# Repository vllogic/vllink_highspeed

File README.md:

# Vllink HighSpeed

## 简介

Vllink Highspeed是一款中低成本高性能调试器。相比Lite版，支持USB2.0高速、更好的IO时序优化、更好的CPU速度，预计JTAG/SWD接口对目标芯片SRAM速度可以达到MB/S的级别，媲美当前千元级别调试器。

## 硬件

## 功能
* JTAG/SWD接口(TDI,TMS,TCK,SRST,TDO,TRST)
* 2路独立串口(TX1,RX1,TX2,RX2)，1路共用串口(TDO,SRST)
* 4通道逻辑分析输入口(CH0,CH1,CH2,CH3)
* 具有电平转换电路，同时支持外部参考电源与内部数字可调电源1.5V至4.75V(Vdrv)
* 使用内部电源对外供电时，支持电流测量(Vdrv)
* OLED_12864(全彩LED可选)
* 远超同等价格级别硬件的Code/Data空间

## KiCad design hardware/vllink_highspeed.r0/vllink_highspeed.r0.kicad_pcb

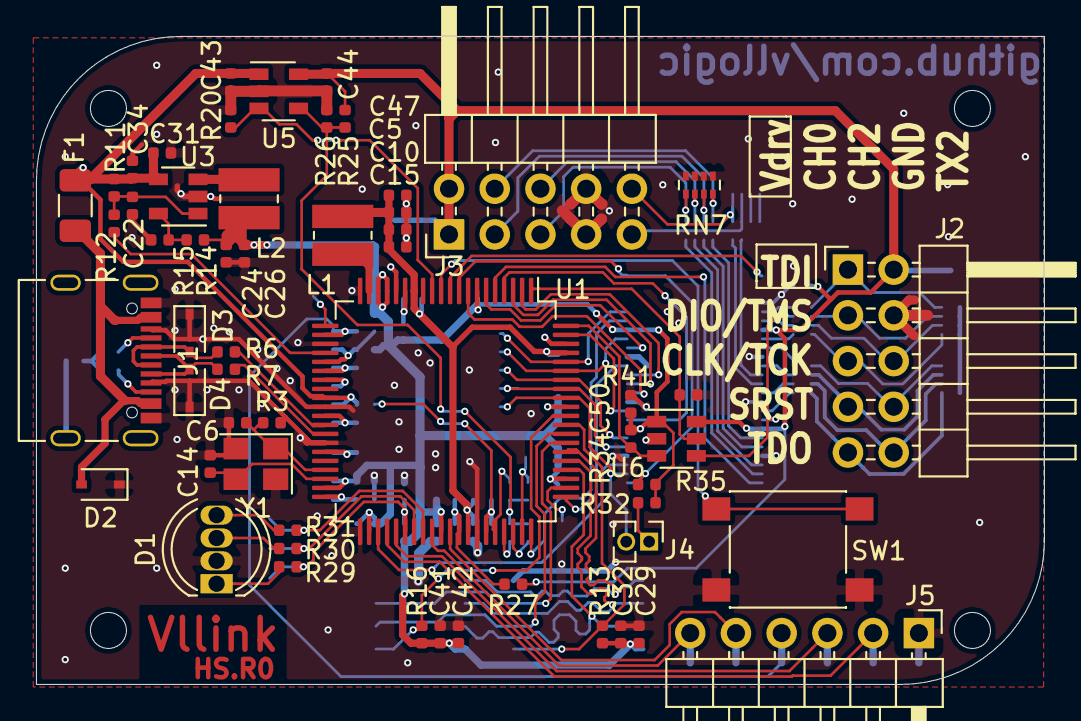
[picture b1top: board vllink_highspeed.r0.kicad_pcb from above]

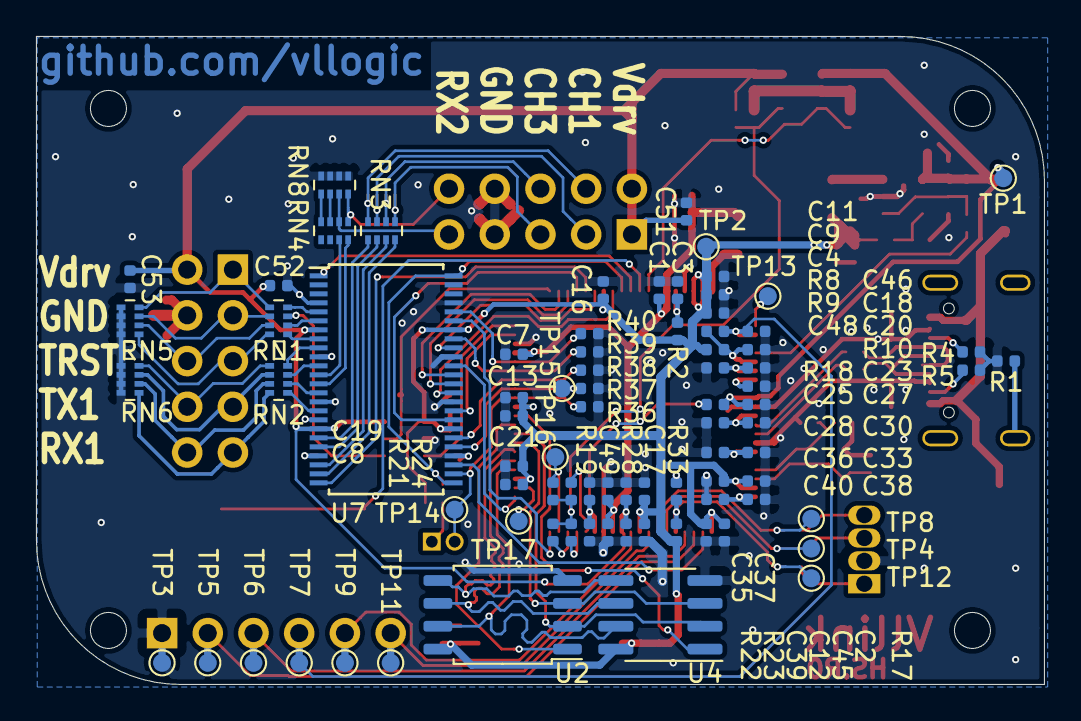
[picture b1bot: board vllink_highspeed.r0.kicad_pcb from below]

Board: 2 copper layers, 56.0 x 36.0 mm, 139 parts (82 on the bottom side), 106 nets.

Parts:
C1, C3, C4, C7, C11, C12, C15, C18, C20, C22, C26, C30, C33, C35, C38: 0.22uF; C_0402_1005Metric
C2, C8, C13, C16, C27, C29, C31, C39, C41, C45, C46, C50, C52: 0.1uF; C_0402_1005Metric
C5, C10, C24, C25, C34, C43, C44, C47, C51, C53: 10uF; C_0402_1005Metric
C6, C14: 12pF; C_0402_1005Metric
C9, C17, C19, C21, C28, C36, C40, C48, C49: 4.7uF; C_0402_1005Metric
C23, C32, C37, C42: 1uF; C_0402_1005Metric
D1: LED_RCGB; LED_D5.0mm-4_RGB
D2, D3, D4: LESD3Z5.0C; D_SOD-323
F1: Polyfuse,2A; Fuse_1206_3216Metric
J1: USB_C_Receptacle_USB2.0; USB_C_Receptacle_Palconn_UTC16-G
J2: JTAG/SWD/UART0; PinHeader_2x05_P2.54mm_Horizontal
J3: LogicIN/UART1; PinHeader_2x05_P2.54mm_Horizontal
J4: NC; PinHeader_1x02_P1.27mm_Vertical
J5: Debug; PinHeader_1x06_P2.54mm_Horizontal
L1, L2: 4.7uH; L_Wuerth_MAPI-3012
R1, R9, R10: 0; R_0402_1005Metric
R2: 30k; R_0402_1005Metric
R3: 2.2M; R_0402_1005Metric
R4, R5: 5.1k; R_0402_1005Metric
R6, R7: 22; R_0402_1005Metric
R8, R20, R33: 10k; R_0402_1005Metric
R11, R25: 100k,1%; R_0402_1005Metric
R12, R17: 10k,NC; R_0402_1005Metric
R13, R16, R35, R36, R37, R38, R39, R40, R41: 47k; R_0402_1005Metric
R14: 274k,1%; R_0402_1005Metric
R15, R18, R19, R21, R27, R28: 60.4k,1%; R_0402_1005Metric
R22: 121k,1%; R_0402_1005Metric
R23: 243k,1%; R_0402_1005Metric
R24, R26: 412k,1%; R_0402_1005Metric
R29, R30, R31, R32: 4.7k; R_0402_1005Metric
R34: 47k,NC; R_0402_1005Metric
RN1, RN2, RN3, RN4: 220; R_Array_Concave_4x0402
RN5, RN6, RN7, RN8: 220k; R_Array_Concave_4x0402
SW1: SW_Push; SW_SPST_PTS645
TP1, TP2, TP3, TP4, TP5, TP6, TP7, TP8, TP9, TP11, TP12, TP13, TP14, TP15, TP16, TP17: TestPoint; TestPoint_Pad_D1.0mm
U1: MIMXRT1011; LQFP-80_12x12mm_P0.5mm
U2: W25Q128JVS; SOIC-8_5.23x5.23mm_P1.27mm
U3: ETA3486; SOT-23-5
U4: PSRAM, NC; SOIC-8_3.9x4.9mm_P1.27mm
U5: SGM2019-ADJ; SOT-23-5
U6: 74LVC1T45GW; SOT-23-6
U7: 74ALVC164245DGG; TSSOP-48_6.1x12.5mm_P0.5mm
Y1: 24M, 12pF; Crystal_SMD_3225-4Pin_3.2x2.5mm

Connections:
/BOOT_CFG0: R38.2, U1.74, U7.30
/BOOT_CFG1: R39.2, U1.75, U7.41
/BOOT_CFG2: R40.2, U1.76, U7.44
/BOOT_MODE0: J4.2, R36.2, TP14.1, U1.72, U7.26
/BOOT_MODE1: R37.2, TP15.1, U1.73, U7.29
/DCDC_3V3: C2.1, C4.1, C8.1, C9.1, C11.1, C13.1, C16.1, C17.1, C19.1, C21.1, C24.1, C26.1, C29.1, C32.1, C33.1, C35.1, C36.1, C37.1, C41.1, C42.1, C50.2, L2.1, R2.1, R9.2, R13.1, R14.1, R16.1, R17.1, R32.2, R34.1, R35.2, TP2.1, U1.7, U1.17, U1.18, U1.39, U1.42, U1.50, U1.63, U1.71, U2.8, U4.8, U6.1, U7.31, U7.42
/DCDC_SWITCH: C3.1, R2.2, U1.15
/FIO_LOGIC3: U1.43, U7.27
/FIO_TDO|UART2_RX: U1.79, U7.33
/FIO_TMS_DIR: R41.2, U1.1, U6.5
/FIO_TMS_I: U1.4, U7.32
/FIO_TMS_O: R34.2, U1.80, U6.3
/FIO|UART1_RX: U1.3, U7.36
/FIO|UART1_TX: U1.2, U7.37
/FSPI_A_CLK: U1.65, U2.6, U4.6
/FSPI_A_D0: U1.66, U2.5, U4.5
/FSPI_A_D1: U1.68, U2.2, U4.2
/FSPI_A_D2: U1.67, U2.3, U4.3
/FSPI_A_D3: U1.64, U2.7, U4.7
/FSPI_A_DQS: TP17.1, U1.62
/FSPI_A_SS0: R13.2, U1.69, U2.1
/FSPI_A_SS1: R16.2, U1.70, U4.1
/GIO_IN_DIR: U1.5, U7.24
/GIO_OE: R35.1, U1.9, U7.25, U7.48
/GIO_OUT_DIR: U1.10, U7.1
/GIO_SRST: U1.61, U7.38
/GIO_TRST|UART2_TX: U1.60, U7.43
/IO_TMS: RN1.3, U6.4, U7.17
/I_LOGIC0: RN3.2, U7.20
/I_LOGIC1: RN3.1, U7.19
/I_LOGIC2: RN3.4, U7.23
/I_LOGIC3: RN3.3, U7.22
/I_RX1: RN2.2, U7.14
/I_RX2: RN4.4, U7.13
/I_TDO: RN2.1, U7.16
/JTAG_MOD: R17.2, R29.2, R33.2, TP12.1, U1.46
/JTAG_TCK: J5.3, TP6.1, U1.45
/JTAG_TDI: R30.2, TP4.1, U1.47
/JTAG_TDO: R31.2, TP8.1, U1.48
/JTAG_TMS: J5.2, TP5.1, U1.44
/JTAG_TRSTB: J5.6, TP11.1, U1.49
/KEY: SW1.1, U1.11
/LOGIC_IN0: J3.3, RN3.7, RN7.3
/LOGIC_IN1: J3.4, RN3.8, RN7.4
/LOGIC_IN2: J3.5, RN3.5, RN7.1
/LOGIC_IN3: J3.6, RN3.6, RN7.2
/ONOFF: TP13.1, U1.21
/OTG1_DN: R6.1, U1.32
/OTG1_DP: R7.1, U1.33
/O_SRST: RN2.3, U7.11
/O_TCK: RN1.1, U7.8
/O_TDI: RN1.4, U7.5
/O_TRST: RN1.2, U7.6
/O_TX1: RN2.4, U7.9
/O_TX2: RN4.3, U7.12
/PMIC_ON_REQ: R12.2, U1.24
/POR_B: C46.1, J5.4, R8.1, TP7.1, U1.22
/RX.1: J2.10, RN2.7, RN6.2
/RX.2: J3.10, RN4.5, RN8.4
/SRST|SWRST: J2.7, RN2.6, RN6.3
/TCK|SWCLK: J2.5, RN1.8, RN5.1
/TDI: J2.1, RN1.5, RN5.4
/TDO|SWO: J2.9, RN2.8, RN6.1
/TMS|SWDIO: J2.3, RN1.6, RN5.3
/TRACE_SWO: R21.2, TP16.1, U1.59
/TRST: J2.6, RN1.7, RN5.2
/TX.1: J2.8, RN2.5, RN6.4
/TX.2: J3.9, RN4.6, RN8.3
/UART3_RX: J5.5, TP9.1, U1.51
/UART4_RX: U1.8, U7.35
/UART4_TX: U1.6, U7.40
/USB_5V: C23.1, C31.1, C34.1, C43.1, F1.1, R11.2, R18.1, TP1.1, U1.29, U3.4, U5.1
/USB_DN: D3.2, J1.A7, J1.B7, R6.2
/USB_DP: D4.2, J1.A6, J1.B6, R7.2
/VBUS_AD: C39.1, R18.2, R19.1, U1.55
/VDD_SNVS_IN: C18.1, R8.2, R9.1, U1.25
/VDD_SOC_IN: C1.1, C5.1, C7.1, C10.1, C12.1, C15.1, C47.1, C49.1, L1.1, U1.14, U1.53, U1.77
/Vdirve_AD: C45.1, R27.2, R28.1, U1.52
/Vdrive_CTRL2: R22.2, U1.58
/Vdrive_CTRL3: R23.2, U1.57
/Vdrive_CTRL4: R24.2, U1.56
/Vdrive_EN: R20.1, U1.12, U5.3
/XTALI: C6.1, R3.1, U1.37, Y1.1
/XTALO: C14.1, U1.38, Y1.3
GND: C1.2, C2.2, C3.2, C4.2, C5.2, C6.2, C7.2, C8.2, C9.2, C10.2, C11.2, C12.2, C13.2, C14.2, C15.2, C16.2, C17.2, C18.2, C19.2, C20.2, C21.2, C22.2, C23.2, C24.2, C25.2, C26.2, C27.2, C28.2, C29.2, C30.2, C31.2, C32.2, C33.2, C34.2, C35.2, C36.2, C37.2, C38.2, C39.2, C40.2, C41.2, C42.2, C43.2, C44.2, C45.2, C46.2, C47.2, C48.2, C49.2, C50.1, C51.2, C52.1, C53.2, D1.2, D2.1, D3.1, D4.1, J1.A1, J1.A8, J1.A12, J1.B1, J1.B8, J1.B12, J2.4, J3.7, J3.8, J5.1, R1.2, R3.2, R4.1, R5.1, R10.2, R15.2, R19.2, R20.2, R26.2, R28.2, R33.1, R36.1, R37.1, R38.1, R39.1, R40.1, R41.1, RN5.5, RN5.6, RN5.7, RN5.8, RN6.5, RN6.6, RN6.7, RN6.8, RN7.5, RN7.6, RN7.7, RN7.8, RN8.5, RN8.6, RN8.7, RN8.8, SW1.2, TP3.1, U1.16, U1.20, U1.23, U1.30, U1.34, U1.41, U1.54, U1.78, U2.4, U3.2, U4.4, U5.2, U6.2, U7.4, U7.10, U7.15, U7.21, U7.28, U7.34, U7.39, U7.45, Y1.2, Y1.4
unnamed: C20.1, C48.1, U1.26
unnamed: C22.1, R11.1, R12.1, U3.1
unnamed: C25.1, C27.1, U1.31
unnamed: C28.1, C30.1, U1.35
unnamed: C38.1, C40.1, U1.40
unnamed: D1.1, R29.1
unnamed: D1.3, R30.1
unnamed: D1.4, R31.1
unnamed: D2.2, F1.2, J1.A4, J1.A9, J1.B4, J1.B9
unnamed: J1.A5, R4.2
unnamed: J1.B5, R5.2
unnamed: J1.S1, R1.1
unnamed: J4.1, R32.1
unnamed: L1.2, U1.19
unnamed: L2.2, U3.3
unnamed: R10.1, U1.27
unnamed: R14.2, R15.1, U3.5
unnamed: R21.1, R22.1, R23.1, R24.1, R25.2, R26.1, U5.4
unnamed: RN4.7, RN8.2
unnamed: RN4.8, RN8.1
Vdrive: C44.1, C51.1, C52.2, C53.1, J2.2, J3.1, J3.2, R25.1, R27.1, U5.5, U6.6, U7.7, U7.18

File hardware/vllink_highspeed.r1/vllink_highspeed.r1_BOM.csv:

"Comment","Description","Designator","Footprint","LibRef","Pins","Quantity","PartNumber","url",
"0.22uF","desc","C26,C15,","C_0402_1005Metric","libref","2","2","","",
"10uF","desc","C43,C44,C47,C34,C24,C10,C5,","C_0402_1005Metric","libref","2","7","","",
"0.1uF","desc","C52,C50,C31,","C_0402_1005Metric","libref","2","3","","",
"BAT60A, NC","desc","D1,","D_SOD-323","libref","2","1","","",
"LESD3Z5.0C","desc","D2,","D_SOD-323","libref","2","1","","",
"BAT60A","desc","D5,","D_SOD-323","libref","2","1","","",
"Polyfuse,2A","desc","F1,","Fuse_1206_3216Metric","libref","2","1","","",
"4.7uH","desc","L1,L2,","L_Wuerth_MAPI-3012","libref","2","2","","",
"4.7k","desc","R32,","R_0402_1005Metric","libref","2","1","","",
"22","desc","R7,R6,","R_0402_1005Metric","libref","2","2","","",
"220","desc","RN4,RN3,","R_Array_Concave_4x0402","libref","8","2","","",
"SW_Push","desc","SW1,","SW_SPST_PTS645","libref","4","1","","",
"MIMXRT1011","desc","U1,","LQFP-80_12x12mm_P0.5mm","libref","80","1","","",
"ETA3486","desc","U3,","SOT-23-5","libref","5","1","","",
"W25Q128JVS","desc","U4,","SOIC-8_P1.27mm_Common","libref","8","1","","",
"SGM2019-ADJ","desc","U5,","SOT-23-5","libref","5","1","","",
"74LVC1T45GW","desc","U6,","SOT-363_SC-70-6","libref","6","1","","",
"24M, 12pF","desc","Y1,","Crystal_SMD_3225-4Pin_3.2x2.5mm","libref","4","1","","",
"12pF","desc","C14,C6,","C_0402_1005Metric","libref","2","2","","",
"0.22uF","desc","C38,C35,C33,C30,C22,C20,C18,C12,C11,C7,C4,C3,C1,","C_0402_1005Metric","libref","2","13","","",
"1uF","desc","C42,C37,C32,C23,","C_0402_1005Metric","libref","2","4","","",
"4.7uF","desc","C49,C48,C40,C36,C28,C21,C19,C17,C9,","C_0402_1005Metric","libref","2","9","","",
"10uF","desc","C53,C51,C25,","C_0402_1005Metric","libref","2","3","","",
"0.1uF","desc","C54,C46,C41,C45,C39,C29,C27,C16,C13,C8,C2,","C_0402_1005Metric","libref","2","11","","",
"LESD3Z5.0C","desc","D4,D3,","D_SOD-323","libref","2","2","","",
"0,NC","desc","R12,","R_0402_1005Metric","libref","2","1","","",
"47k","desc","R13,R30,R41,R40,R39,R38,R37,R36,R35,R16,R20,R33,","R_0402_1005Metric","libref","2","12","","",
"274k,1%","desc","R14,","R_0402_1005Metric","libref","2","1","","",
"30k","desc","R2,","R_0402_1005Metric","libref","2","1","","",
"121k,1%","desc","R22,","R_0402_1005Metric","libref","2","1","","",
"243k,1%","desc","R23,","R_0402_1005Metric","libref","2","1","","",
"475k,1%","desc","R24,","R_0402_1005Metric","libref","2","1","","",
"100k,1%","desc","R25,R11,","R_0402_1005Metric","libref","2","2","","",
"412k,1%","desc","R26,","R_0402_1005Metric","libref","2","1","","",
"60.4k,1%","desc","R28,R27,R21,R19,R18,R15,","R_0402_1005Metric","libref","2","6","","",
"0.05, 1%, 1206","desc","R29,","R_1206_3216Metric","libref","2","1","","",
"2.2M","desc","R3,","R_0402_1005Metric","libref","2","1","","",
"47k,NC","desc","R34,R17,","R_0402_1005Metric","libref","2","2","","",
"4.7k","desc","R43,R42,R31,","R_0402_1005Metric","libref","2","3","","",
"0","desc","R44,R10,R9,R1,","R_0402_1005Metric","libref","2","4","","",
"5.1k","desc","R5,R4,","R_0402_1005Metric","libref","2","2","","",
"10k","desc","R8,","R_0402_1005Metric","libref","2","1","","",
"220","desc","RN2,RN1,","R_Array_Concave_4x0402","libref","8","2","","",
"220k","desc","RN8,RN7,RN6,RN5,","R_Array_Concave_4x0402","libref","8","4","","",
"TestPoint","desc","TP17,TP16,TP15,TP13,TP12,TP11,TP9,TP8,TP7,TP6,TP5,TP4,TP3,TP2,TP1,TP14,","TestPoint_Pad_D1.0mm","libref","1","16","","",
"LY68L6400","desc","U2,","SOIC-8_P1.27mm_Common","libref","8","1","","",
"74ALVC164245DGG","desc","U7,","TSSOP-48_6.1x12.5mm_P0.5mm","libref","48","1","","",
"TP199A2/TP181A2","desc","U8,","SOT-363_SC-70-6","libref","6","1","","",
"Through Hole Items ",
"LED_RCGB","desc","D6,","LED_D5.0mm-4_RGB","libref","4","1","","",
"USB_C_Receptacle_USB2.0","desc","J1,","USB_C_Receptacle_Palconn_UTC16-G","libref","22","1","","",
"JTAG/SWD/UART0","desc","J2,","IDC-Header_2x05_P2.54mm_Horizontal","libref","10","1","","",
"LogicIN/UART1","desc","J3,","IDC-Header_2x05_P2.54mm_Horizontal","libref","10","1","","",
"Mode","desc","J4,","PinHeader_1x02_P1.27mm_Vertical","libref","2","1","","",
"SWD","desc","J5,","PinHeader_1x04_P2.54mm_Vertical","libref","4","1","","",
"UART","desc","J6,","PinHeader_1x02_P2.54mm_Vertical","libref","2","1","","",
"Vdrive_I","desc","J7,","PinHeader_1x01_P2.54mm_Vertical","libref","1","1","","",
"OLED_12864","desc","OLED1,","OLED_12864","libref","11","1","","",

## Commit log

2021-01-22 add vllink_highspeed pcb files
2021-01-22 remove vsf/project_vllink_lite/
2021-12-18 vllink_basic\hardware.version1
